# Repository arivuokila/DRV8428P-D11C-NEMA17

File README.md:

# DRV8428P-D11C-NEMA17

Modification of the board by Neil Gershenfeld http://academy.cba.mit.edu/classes/output_devices/DRV8428/hello.DRV8428-D11C-NEMA17.png for DRV8428P bipolar stepper or dual brushed motor driver

DRV8428P https://www.ti.com/store/ti/en/p/product/?p=DRV8428PPWPR

Bootloader for the D11C can be burnt with for example fabbed SWD programmer: https://gitlab.fabcloud.org/pub/programmers/programmer-swd-d11c

After the D11C has the bootloader, programs can be uploaded directly via USB with e.g. Arduino IDE
https://github.com/qbolsee/ArduinoCore-fab-sam
https://raw.githubusercontent.com/qbolsee/ArduinoCore-fab-sam/master/json/package_Fab_SAM_index.json

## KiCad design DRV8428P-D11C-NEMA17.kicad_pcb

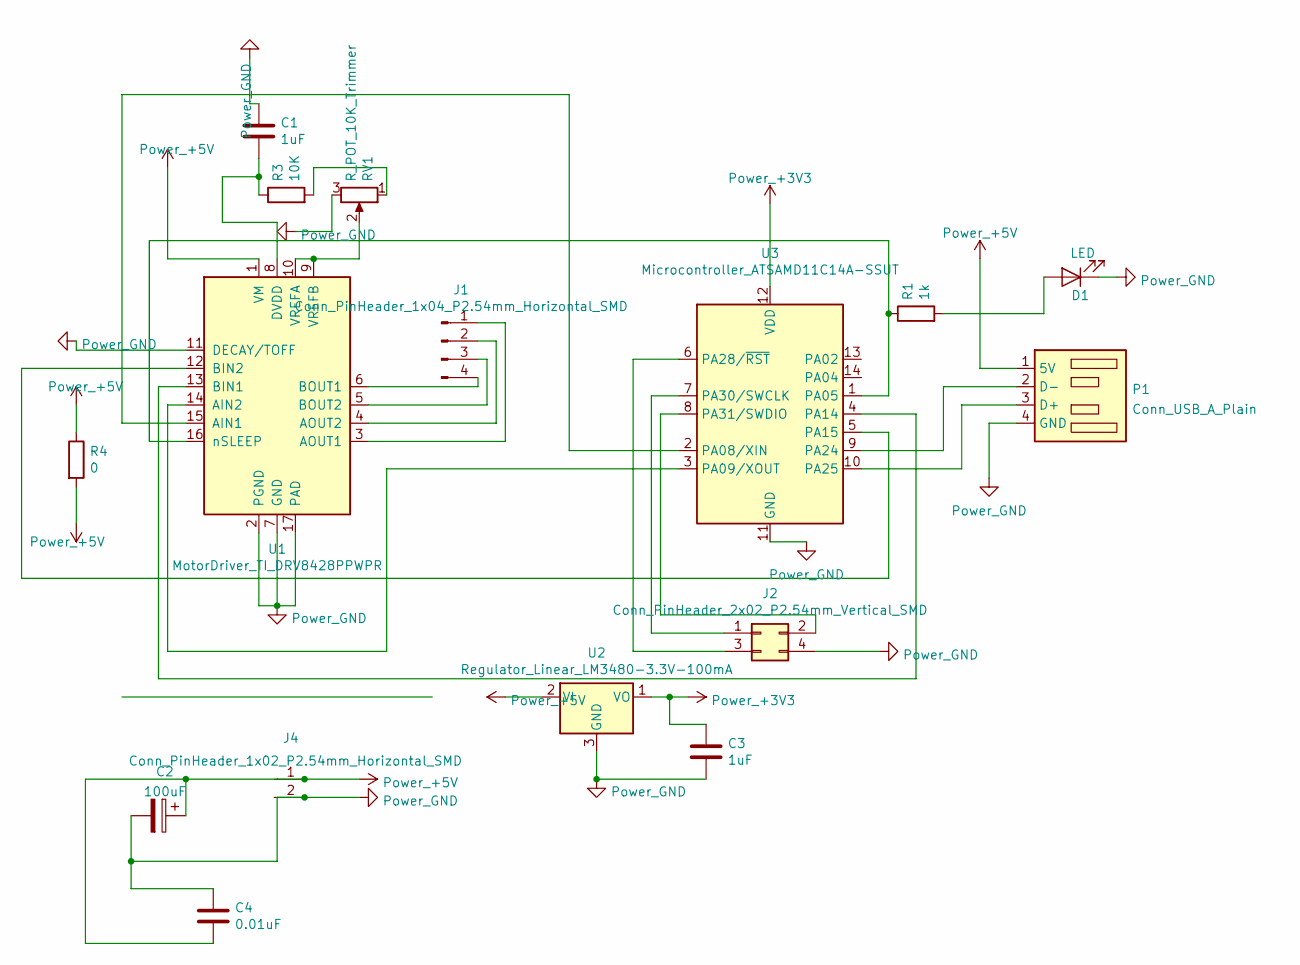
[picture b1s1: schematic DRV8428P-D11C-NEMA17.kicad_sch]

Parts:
C1, C3: 1uF; C_1206
C2: 100uF; CP_Elec_10x10mm
C4: 0.01uF; C_1206
D1: LED; LED_1206
J1: Conn_PinHeader_1x04_P2.54mm_Horizontal_SMD; PinHeader_1x04_P2.54mm_Horizontal_SMD
J2: Conn_PinHeader_2x02_P2.54mm_Vertical_SMD; PinHeader_2x02_P2.54mm_Vertical_SMD
J4: Conn_PinHeader_1x02_P2.54mm_Horizontal_SMD; PinHeader_UPDI_01x02_P2.54mm_Horizontal_SMD
P1: Conn_USB_A_Plain
R1: 1k; R_1206
R3: 10K; R_1206
R4: 0; R_1206
RV1: R_POT_10K_Trimmer; Potentiometer_TT_Model-23_4.5x5.0x3.0mm
U1: MotorDriver_TI_DRV8428PPWPR; HTSSOP-16
U2: Regulator_Linear_LM3480-3.3V-100mA; SOT-23
U3: Microcontroller_ATSAMD11C14A-SSUT; SOIC-14_3.9x8.7mm_P1.27mm

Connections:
+3V3: C3.1, U2.1 (VO), U3.12 (VDD)
+5V: C2.1, C4.2, J4.1, P1.1 (5V), R4.1, R4.2, U1.1 (VM), U2.2 (VI)
GND: C1.1, C2.2, C3.2, C4.1, D1.1 (K), J2.4, J4.2, P1.4 (GND), RV1.3, U1.2 (PGND), U1.7 (GND), U1.11 (DECAY/TOFF), U1.17 (PAD), U2.3 (GND), U3.11 (GND)
unnamed: C1.2, R3.1, U1.8 (DVDD)
unnamed: J1.1, U1.3 (AOUT1)
unnamed: J1.2, U1.4 (AOUT2)
unnamed: J1.3, U1.5 (BOUT2)
unnamed: J1.4, U1.6 (BOUT1)
unnamed: J2.1, U3.7 (PA30/SWCLK)
unnamed: J2.2, U3.8 (PA31/SWDIO)
unnamed: J2.3, U3.6 (PA28/~RST)
unnamed: P1.2 (D-), U3.9 (PA24)
unnamed: P1.3 (D+), U3.10 (PA25)
unnamed: D1.2 (A), R1.2
unnamed: R3.2, RV1.1
unnamed: RV1.2, U1.9 (VREFB), U1.10 (VREFA)
unnamed: U1.12 (BIN2), U3.5 (PA15)
unnamed: U1.14 (AIN2), U3.3 (PA09/XOUT)
unnamed: R1.1, U1.16 (nSLEEP), U3.1 (PA05)
unnamed: U1.15 (AIN1), U3.2 (PA08/XIN)
unnamed: U1.13 (BIN1), U3.4 (PA14)

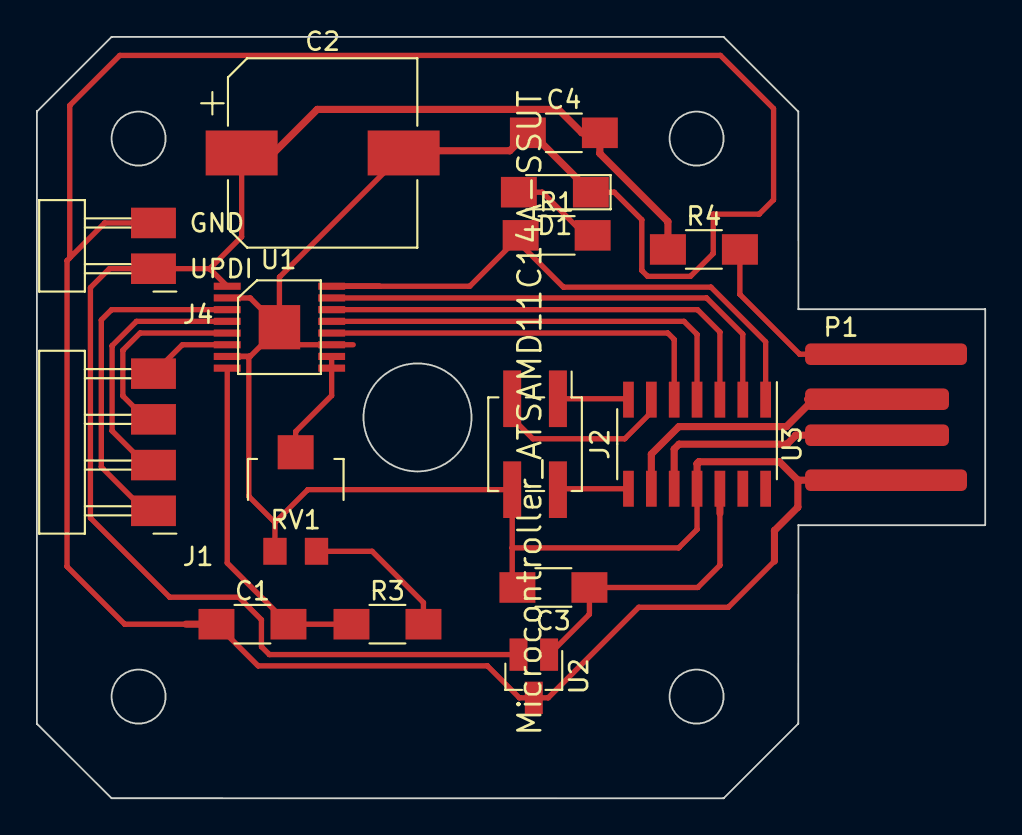
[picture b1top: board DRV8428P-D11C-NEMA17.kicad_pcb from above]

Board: 2 copper layers, 52.7 x 42.3 mm, 16 parts (0 on the bottom side), 21 nets.

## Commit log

2022-01-25 Design files for Kicad
2022-01-25 Create Gerber
2022-01-28 USB fixed
2022-01-28 Updated board
2022-02-04 Updating the design
2022-02-04 Updating the gerbers
2023-04-03 Add files via upload
    Code to run single steps with f and r buttons via serial 115200 bps
